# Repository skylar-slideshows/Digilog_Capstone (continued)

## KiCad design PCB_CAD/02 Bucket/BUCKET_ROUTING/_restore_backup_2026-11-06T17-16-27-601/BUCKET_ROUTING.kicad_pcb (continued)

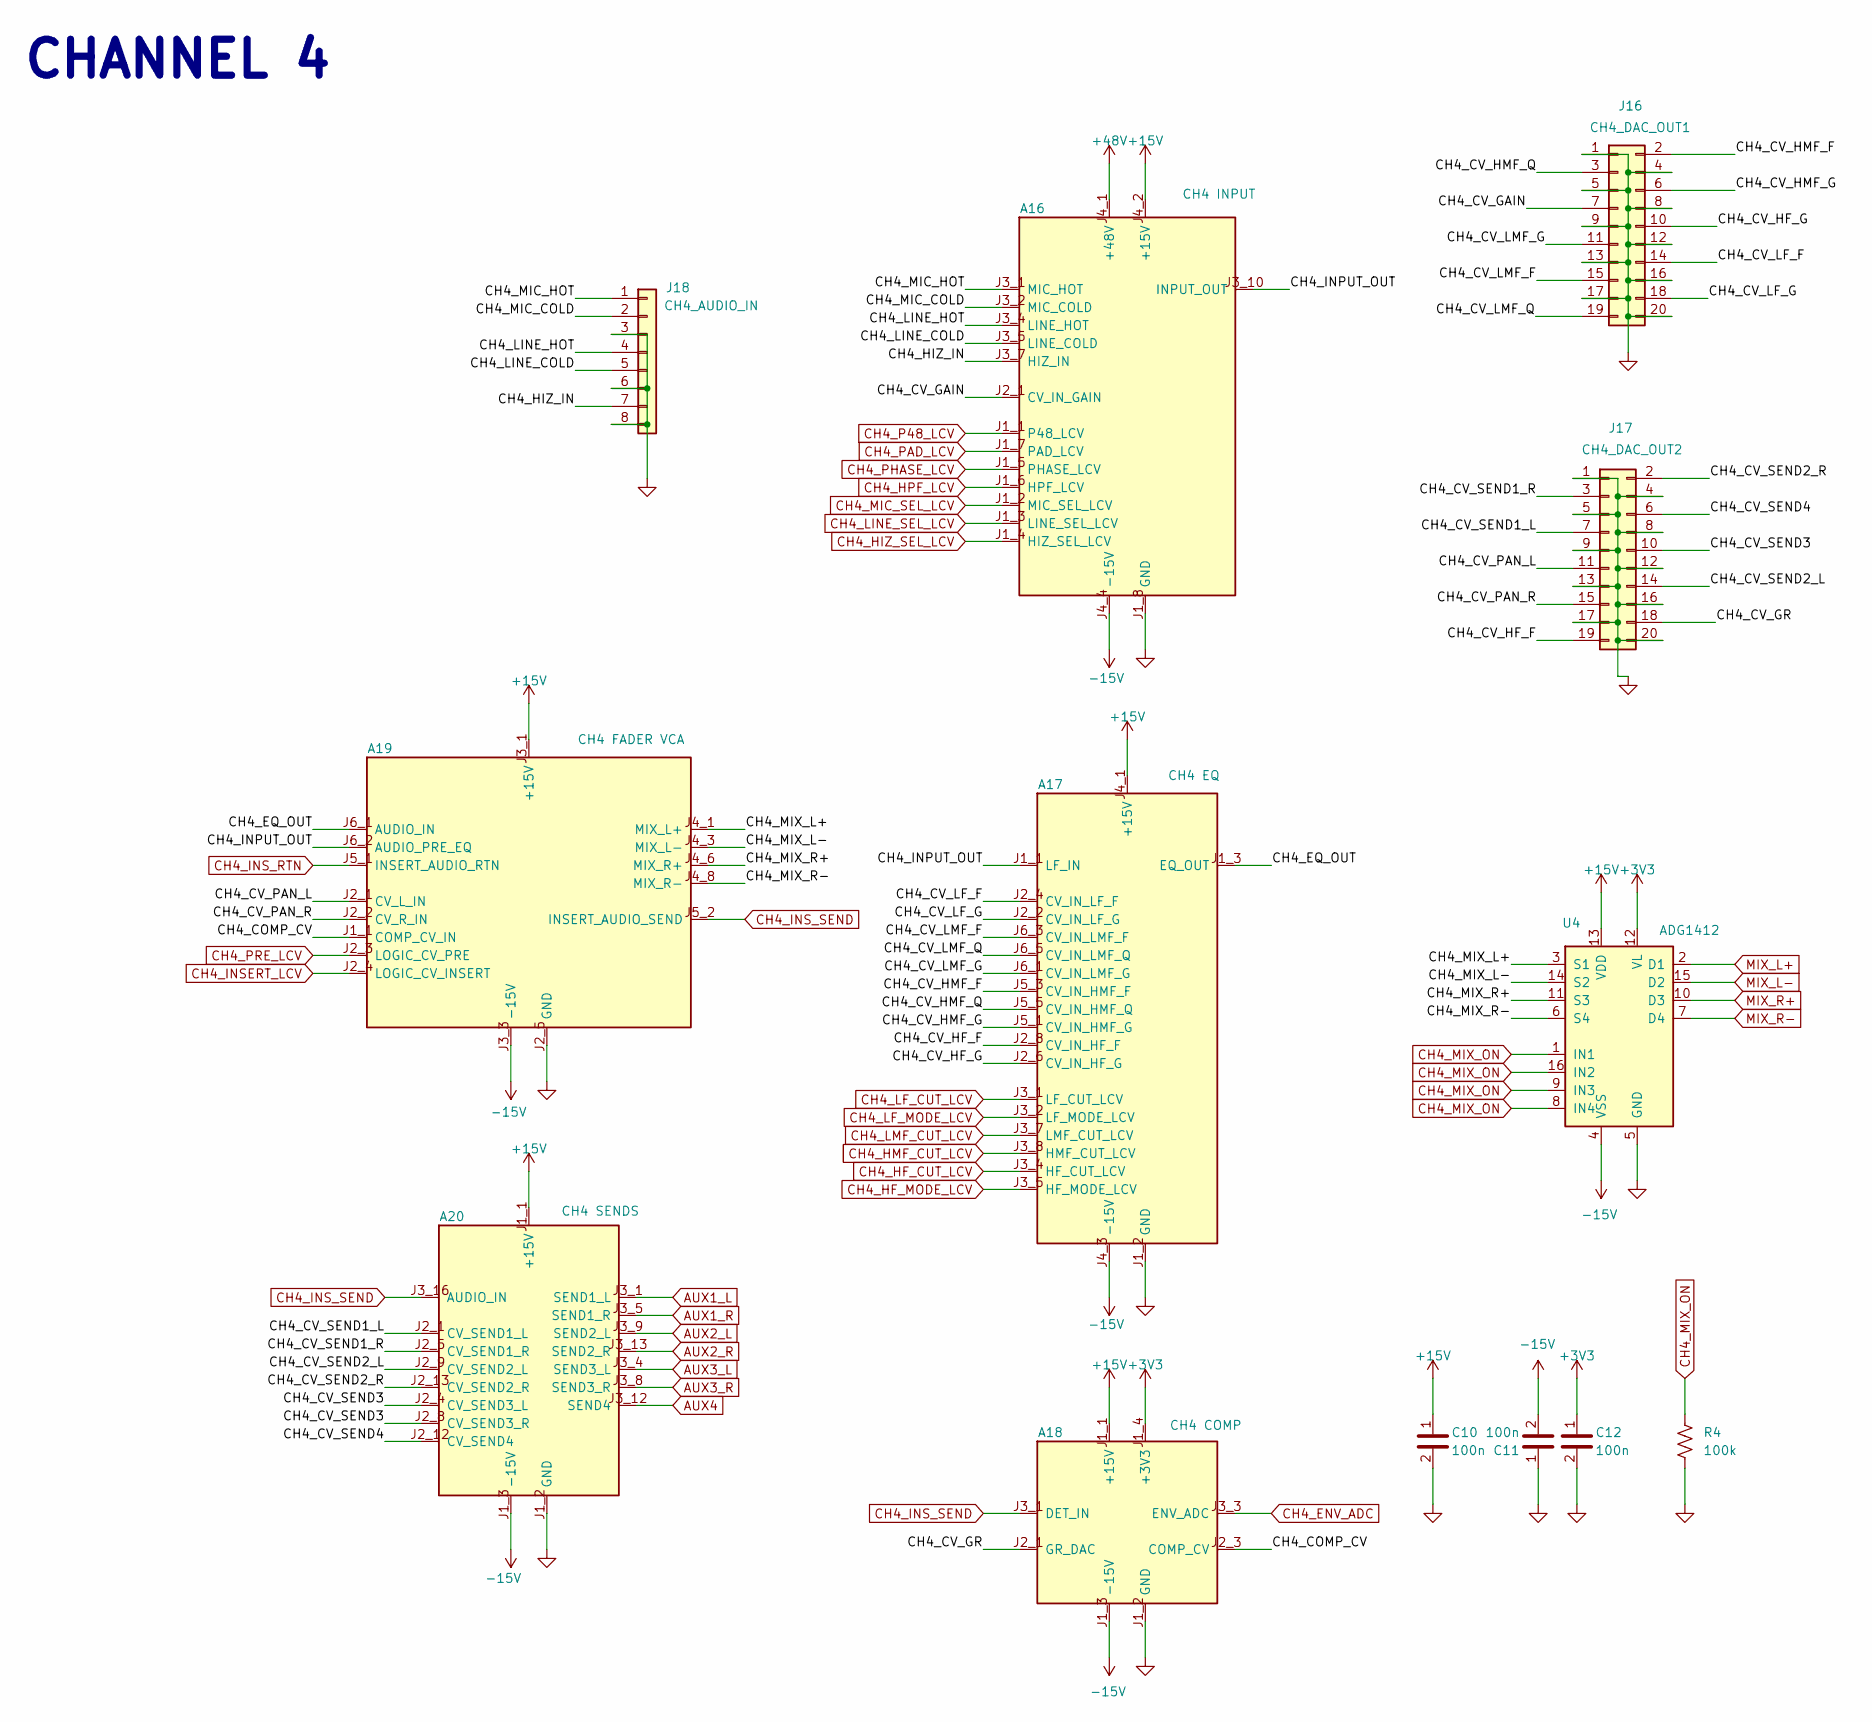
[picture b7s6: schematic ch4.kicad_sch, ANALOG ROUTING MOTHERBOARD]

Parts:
A16: CH4 INPUT; INPUT_CARD; LCSC dnp
A17: CH4 EQ; EQ_CARD; LCSC dnp
A18: CH4 COMP; COMP_CARD; LCSC dnp
A19: CH4 FADER VCA; FADER_VCA_CARD; LCSC dnp
A20: CH4 SENDS; SENDS_CARD; LCSC dnp
C10, C11, C12: 100n; C_0603_1608Metric; LCSC C1591
J16: CH4_DAC_OUT1; PinHeader_2x10_P1.27mm_Vertical; LCSC C42455943
J17: CH4_DAC_OUT2; PinHeader_2x10_P1.27mm_Vertical; LCSC C42455943
J18: CH4_AUDIO_IN; PinHeader_1x08_P2.54mm_Vertical; LCSC C54620384
R4: 100k; R_0603_1608Metric; LCSC C122538
U4: ADG1412; TSSOP-16_4.4x5mm_P0.65mm; LCSC C206604

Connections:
+3V3: A18.J1_4 (+3V3), C12.1, U4.12 (VL); also elsewhere on the board
+15V: A16.J4_2 (+15V), A17.J4_1 (+15V), A18.J1_1 (+15V), A19.J3_1 (+15V), A20.J1_1 (+15V), C10.1, U4.13 (VDD); also elsewhere on the board
+48V: A16.J4_1 (+48V); also elsewhere on the board
-15V: A16.J4_4 (-15V), A17.J4_3 (-15V), A18.J1_3 (-15V), A19.J3_3 (-15V), A20.J1_3 (-15V), C11.2, U4.4 (VSS); also elsewhere on the board
/CH4/CH4_COMP_CV: A18.J2_3 (COMP_CV), A19.J1_1 (COMP_CV_IN)
/CH4/CH4_CV_GAIN: A16.J2_1 (CV_IN_GAIN), J16.7
/CH4/CH4_CV_GR: A18.J2_1 (GR_DAC), J17.18
/CH4/CH4_CV_HF_F: A17.J2_8 (CV_IN_HF_F), J17.19
/CH4/CH4_CV_HF_G: A17.J2_6 (CV_IN_HF_G), J16.10
/CH4/CH4_CV_HMF_F: A17.J5_3 (CV_IN_HMF_F), J16.2
/CH4/CH4_CV_HMF_G: A17.J5_1 (CV_IN_HMF_G), J16.6
/CH4/CH4_CV_HMF_Q: A17.J5_5 (CV_IN_HMF_Q), J16.3
/CH4/CH4_CV_LF_F: A17.J2_4 (CV_IN_LF_F), J16.14
/CH4/CH4_CV_LF_G: A17.J2_2 (CV_IN_LF_G), J16.18
/CH4/CH4_CV_LMF_F: A17.J6_3 (CV_IN_LMF_F), J16.15
/CH4/CH4_CV_LMF_G: A17.J6_1 (CV_IN_LMF_G), J16.11
/CH4/CH4_CV_LMF_Q: A17.J6_5 (CV_IN_LMF_Q), J16.19
/CH4/CH4_CV_PAN_L: A19.J2_1 (CV_L_IN), J17.11
/CH4/CH4_CV_PAN_R: A19.J2_2 (CV_R_IN), J17.15
/CH4/CH4_CV_SEND1_L: A20.J2_1 (CV_SEND1_L), J17.7
/CH4/CH4_CV_SEND1_R: A20.J2_5 (CV_SEND1_R), J17.3
/CH4/CH4_CV_SEND2_L: A20.J2_9 (CV_SEND2_L), J17.14
/CH4/CH4_CV_SEND2_R: A20.J2_13 (CV_SEND2_R), J17.2
/CH4/CH4_CV_SEND3: A20.J2_4 (CV_SEND3_L), A20.J2_8 (CV_SEND3_R), J17.10
/CH4/CH4_CV_SEND4: A20.J2_12 (CV_SEND4), J17.6
/CH4/CH4_EQ_OUT: A17.J1_3 (EQ_OUT), A19.J6_1 (AUDIO_IN)
/CH4/CH4_HIZ_IN: A16.J3_7 (HIZ_IN), J18.7
/CH4/CH4_INPUT_OUT: A16.J3_10 (INPUT_OUT), A17.J1_1 (LF_IN), A19.J6_2 (AUDIO_PRE_EQ)
/CH4/CH4_LINE_COLD: A16.J3_5 (LINE_COLD), J18.5
/CH4/CH4_LINE_HOT: A16.J3_4 (LINE_HOT), J18.4
/CH4/CH4_MIC_COLD: A16.J3_2 (MIC_COLD), J18.2
/CH4/CH4_MIC_HOT: A16.J3_1 (MIC_HOT), J18.1
/CH4/CH4_MIX_L+: A19.J4_1 (MIX_L+), U4.3 (S1)
/CH4/CH4_MIX_L-: A19.J4_3 (MIX_L-), U4.14 (S2)
/CH4/CH4_MIX_R+: A19.J4_6 (MIX_R+), U4.11 (S3)
/CH4/CH4_MIX_R-: A19.J4_8 (MIX_R-), U4.6 (S4)
AUX1_L: A20.J3_1 (SEND1_L); also elsewhere on the board
AUX1_R: A20.J3_5 (SEND1_R); also elsewhere on the board
AUX2_L: A20.J3_9 (SEND2_L); also elsewhere on the board
AUX2_R: A20.J3_13 (SEND2_R); also elsewhere on the board
AUX3_L: A20.J3_4 (SEND3_L); also elsewhere on the board
AUX3_R: A20.J3_8 (SEND3_R); also elsewhere on the board
AUX4: A20.J3_12 (SEND4); also elsewhere on the board
CH4_ENV_ADC: A18.J3_3 (ENV_ADC); also elsewhere on the board
CH4_HF_CUT_LCV: A17.J3_4 (HF_CUT_LCV); also elsewhere on the board
CH4_HF_MODE_LCV: A17.J3_5 (HF_MODE_LCV); also elsewhere on the board
CH4_HIZ_SEL_LCV: A16.J1_4 (HIZ_SEL_LCV); also elsewhere on the board
CH4_HMF_CUT_LCV: A17.J3_8 (HMF_CUT_LCV); also elsewhere on the board
CH4_HPF_LCV: A16.J1_6 (HPF_LCV); also elsewhere on the board
CH4_INSERT_LCV: A19.J2_4 (LOGIC_CV_INSERT); also elsewhere on the board
CH4_INS_RTN: A19.J5_1 (INSERT_AUDIO_RTN); also elsewhere on the board
CH4_INS_SEND: A18.J3_1 (DET_IN), A19.J5_2 (INSERT_AUDIO_SEND), A20.J3_16 (AUDIO_IN); also elsewhere on the board
CH4_LF_CUT_LCV: A17.J3_1 (LF_CUT_LCV); also elsewhere on the board
CH4_LF_MODE_LCV: A17.J3_2 (LF_MODE_LCV); also elsewhere on the board
CH4_LINE_SEL_LCV: A16.J1_3 (LINE_SEL_LCV); also elsewhere on the board
CH4_LMF_CUT_LCV: A17.J3_7 (LMF_CUT_LCV); also elsewhere on the board
CH4_MIC_SEL_LCV: A16.J1_2 (MIC_SEL_LCV); also elsewhere on the board
CH4_MIX_ON: R4.1, U4.1 (IN1), U4.8 (IN4), U4.9 (IN3), U4.16 (IN2); also elsewhere on the board
CH4_P48_LCV: A16.J1_1 (P48_LCV); also elsewhere on the board
CH4_PAD_LCV: A16.J1_7 (PAD_LCV); also elsewhere on the board
CH4_PHASE_LCV: A16.J1_5 (PHASE_LCV); also elsewhere on the board
CH4_PRE_LCV: A19.J2_3 (LOGIC_CV_PRE); also elsewhere on the board
GND: A16.J1_8 (GND), A16.J2_2 (GND), A16.J3_3 (GND), A16.J3_6 (GND), A16.J3_8 (GND), A16.J3_9 (GND), A16.J4_3 (GND), A17.J1_2 (GND), A17.J1_4 (GND), A17.J2_1 (GND), A17.J2_3 (GND), A17.J2_5 (GND), A17.J2_7 (GND), A17.J3_3 (GND), A17.J3_6 (GND), A17.J4_2 (GND), A17.J5_2 (GND), A17.J5_4 (GND), A17.J5_6 (GND), A17.J6_2 (GND), A17.J6_4 (GND), A17.J6_6 (GND), A18.J1_2 (GND), A18.J2_2 (GND), A18.J2_4 (GND), A18.J3_2 (GND), A18.J3_4 (GND), A19.J1_2 (GND), A19.J2_5 (GND), A19.J3_2 (GND), A19.J4_2 (GND), A19.J4_4 (GND), A19.J4_5 (GND), A19.J4_7 (GND), A19.J5_3 (GND), A19.J6_3 (GND), A20.J1_2 (GND), A20.J2_2 (GND), A20.J2_3 (GND), A20.J2_6 (GND), A20.J2_7 (GND), A20.J2_10 (GND), A20.J2_11 (GND), A20.J2_14 (GND), A20.J3_2 (GND), A20.J3_3 (GND), A20.J3_6 (GND), A20.J3_7 (GND), A20.J3_10 (GND), A20.J3_11 (GND), A20.J3_14 (GND), A20.J3_15 (GND), C10.2, C11.1, C12.2, J16.1, J16.4, J16.5, J16.8, J16.9, J16.12, J16.13, J16.16, J16.17, J16.20, J17.1, J17.4, J17.5, J17.8, J17.9, J17.12, J17.13, J17.16, J17.17, J17.20, J18.3, J18.6, J18.8, R4.2, U4.5 (GND); also elsewhere on the board
MIX_L+: U4.2 (D1); also elsewhere on the board
MIX_L-: U4.15 (D2); also elsewhere on the board
MIX_R+: U4.10 (D3); also elsewhere on the board
MIX_R-: U4.7 (D4); also elsewhere on the board

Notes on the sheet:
CHANNEL 4

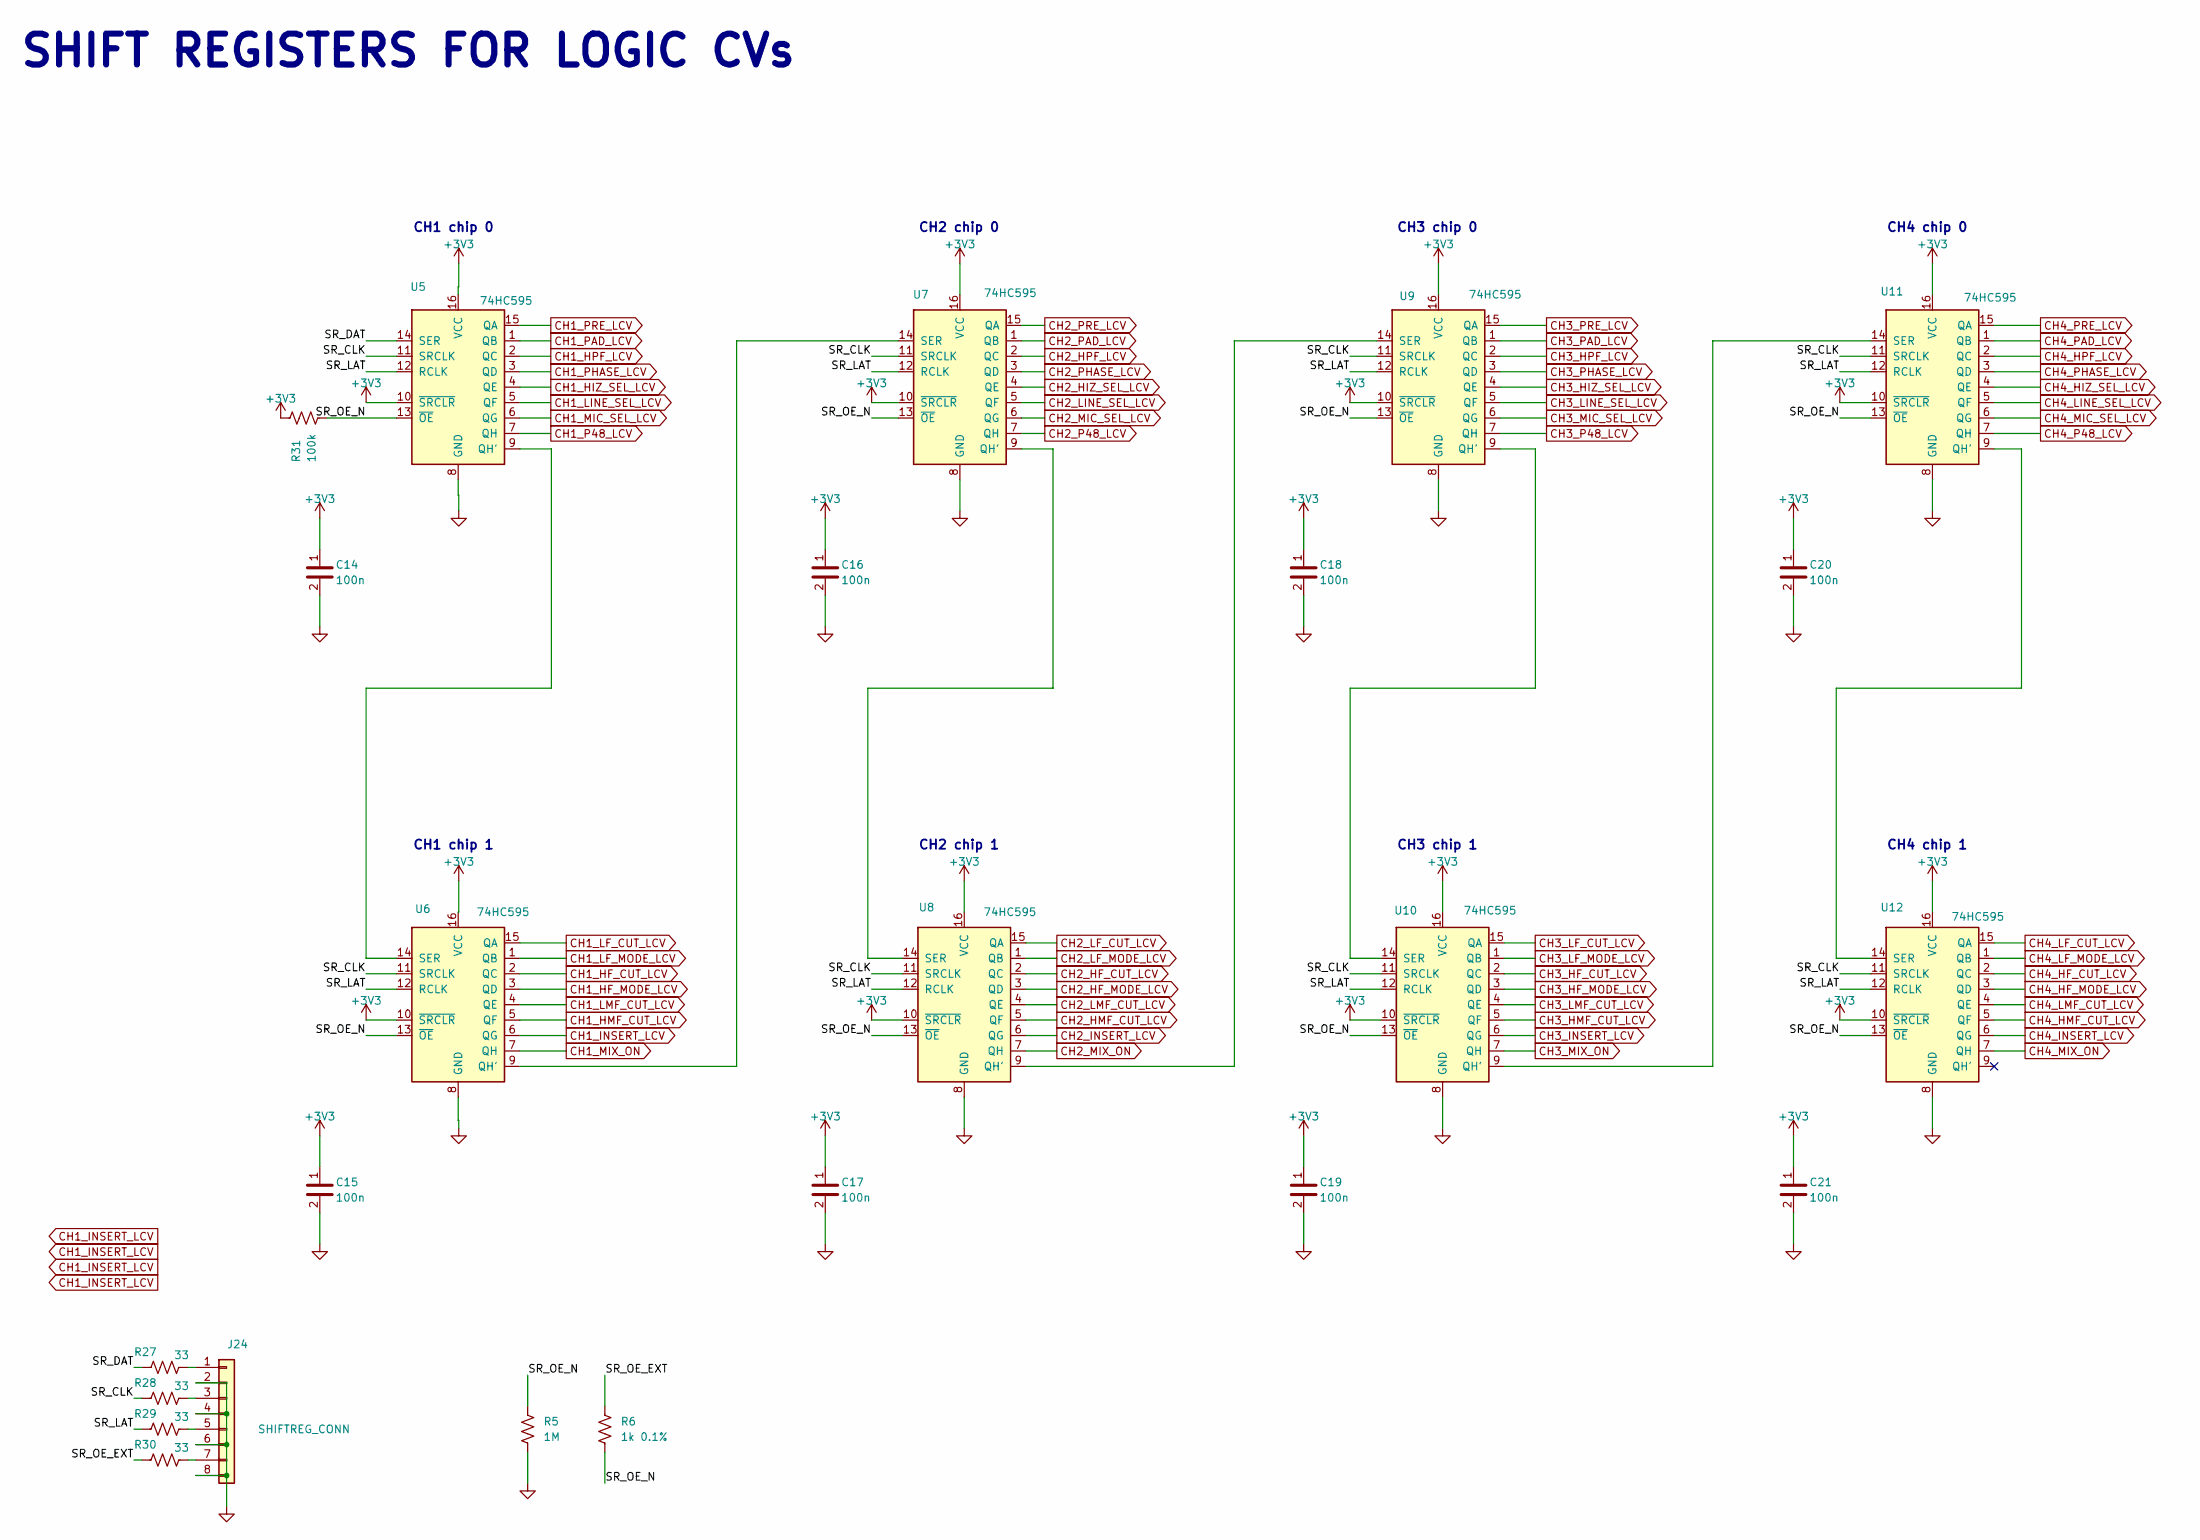
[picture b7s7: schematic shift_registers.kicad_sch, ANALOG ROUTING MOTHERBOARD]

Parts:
C14, C15, C16, C17, C18, C19, C20, C21: 100n; C_0603_1608Metric; LCSC C1591
J24: SHIFTREG_CONN; PinHeader_1x08_P2.54mm_Vertical; LCSC C54620384
R5: 1M; R_0603_1608Metric; LCSC C86472
R6: 1k 0.1%; R_0603_1608Metric; LCSC C110776
R27, R28, R29, R30: 33; R_0603_1608Metric; LCSC C23140
R31: 100k; R_0603_1608Metric; LCSC C122538
U5, U6, U7, U8, U9, U10, U11, U12: 74HC595; TSSOP-16_4.4x5mm_P0.65mm; LCSC C5948

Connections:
+3V3: C14.1, C15.1, C16.1, C17.1, C18.1, C19.1, C20.1, C21.1, R31.1, U5.10 (~SRCLR), U5.16 (VCC), U6.10 (~SRCLR), U6.16 (VCC), U7.10 (~SRCLR), U7.16 (VCC), U8.10 (~SRCLR), U8.16 (VCC), U9.10 (~SRCLR), U9.16 (VCC), U10.10 (~SRCLR), U10.16 (VCC), U11.10 (~SRCLR), U11.16 (VCC), U12.10 (~SRCLR), U12.16 (VCC); also elsewhere on the board
/LOGIC SHIFT REGISTERS/SR_CLK: J24.3, R28.1, R28.2, U5.11 (SRCLK), U6.11 (SRCLK), U7.11 (SRCLK), U8.11 (SRCLK), U9.11 (SRCLK), U10.11 (SRCLK), U11.11 (SRCLK), U12.11 (SRCLK)
/LOGIC SHIFT REGISTERS/SR_DAT: J24.1, R27.1, R27.2, U5.14 (SER)
/LOGIC SHIFT REGISTERS/SR_LAT: J24.5, R29.1, R29.2, U5.12 (RCLK), U6.12 (RCLK), U7.12 (RCLK), U8.12 (RCLK), U9.12 (RCLK), U10.12 (RCLK), U11.12 (RCLK), U12.12 (RCLK)
/LOGIC SHIFT REGISTERS/SR_OE_EXT: J24.7, R6.1, R30.1, R30.2
/LOGIC SHIFT REGISTERS/SR_OE_N: R5.1, R6.2, R31.2, U5.13 (~OE), U6.13 (~OE), U7.13 (~OE), U8.13 (~OE), U9.13 (~OE), U10.13 (~OE), U11.13 (~OE), U12.13 (~OE)
CH1_HF_CUT_LCV: U6.2 (QC); also elsewhere on the board
CH1_HF_MODE_LCV: U6.3 (QD); also elsewhere on the board
CH1_HIZ_SEL_LCV: U5.4 (QE); also elsewhere on the board
CH1_HMF_CUT_LCV: U6.5 (QF); also elsewhere on the board
CH1_HPF_LCV: U5.2 (QC); also elsewhere on the board
CH1_INSERT_LCV: U6.6 (QG); also elsewhere on the board
CH1_LF_CUT_LCV: U6.15 (QA); also elsewhere on the board
CH1_LF_MODE_LCV: U6.1 (QB); also elsewhere on the board
CH1_LINE_SEL_LCV: U5.5 (QF); also elsewhere on the board
CH1_LMF_CUT_LCV: U6.4 (QE); also elsewhere on the board
CH1_MIC_SEL_LCV: U5.6 (QG); also elsewhere on the board
CH1_MIX_ON: U6.7 (QH); also elsewhere on the board
CH1_P48_LCV: U5.7 (QH); also elsewhere on the board
CH1_PAD_LCV: U5.1 (QB); also elsewhere on the board
CH1_PHASE_LCV: U5.3 (QD); also elsewhere on the board
CH1_PRE_LCV: U5.15 (QA); also elsewhere on the board
CH2_HF_CUT_LCV: U8.2 (QC); also elsewhere on the board
CH2_HF_MODE_LCV: U8.3 (QD); also elsewhere on the board
CH2_HIZ_SEL_LCV: U7.4 (QE); also elsewhere on the board
CH2_HMF_CUT_LCV: U8.5 (QF); also elsewhere on the board
CH2_HPF_LCV: U7.2 (QC); also elsewhere on the board
CH2_INSERT_LCV: U8.6 (QG); also elsewhere on the board
CH2_LF_CUT_LCV: U8.15 (QA); also elsewhere on the board
CH2_LF_MODE_LCV: U8.1 (QB); also elsewhere on the board
CH2_LINE_SEL_LCV: U7.5 (QF); also elsewhere on the board
CH2_LMF_CUT_LCV: U8.4 (QE); also elsewhere on the board
CH2_MIC_SEL_LCV: U7.6 (QG); also elsewhere on the board
CH2_MIX_ON: U8.7 (QH); also elsewhere on the board
CH2_P48_LCV: U7.7 (QH); also elsewhere on the board
CH2_PAD_LCV: U7.1 (QB); also elsewhere on the board
CH2_PHASE_LCV: U7.3 (QD); also elsewhere on the board
CH2_PRE_LCV: U7.15 (QA); also elsewhere on the board
CH3_HF_CUT_LCV: U10.2 (QC); also elsewhere on the board
CH3_HF_MODE_LCV: U10.3 (QD); also elsewhere on the board
CH3_HIZ_SEL_LCV: U9.4 (QE); also elsewhere on the board
CH3_HMF_CUT_LCV: U10.5 (QF); also elsewhere on the board
CH3_HPF_LCV: U9.2 (QC); also elsewhere on the board
CH3_INSERT_LCV: U10.6 (QG); also elsewhere on the board
CH3_LF_CUT_LCV: U10.15 (QA); also elsewhere on the board
CH3_LF_MODE_LCV: U10.1 (QB); also elsewhere on the board
CH3_LINE_SEL_LCV: U9.5 (QF); also elsewhere on the board
CH3_LMF_CUT_LCV: U10.4 (QE); also elsewhere on the board
CH3_MIC_SEL_LCV: U9.6 (QG); also elsewhere on the board
CH3_MIX_ON: U10.7 (QH); also elsewhere on the board
CH3_P48_LCV: U9.7 (QH); also elsewhere on the board
CH3_PAD_LCV: U9.1 (QB); also elsewhere on the board
CH3_PHASE_LCV: U9.3 (QD); also elsewhere on the board
CH3_PRE_LCV: U9.15 (QA); also elsewhere on the board
CH4_HF_CUT_LCV: U12.2 (QC); also elsewhere on the board
CH4_HF_MODE_LCV: U12.3 (QD); also elsewhere on the board
CH4_HIZ_SEL_LCV: U11.4 (QE); also elsewhere on the board
CH4_HMF_CUT_LCV: U12.5 (QF); also elsewhere on the board
CH4_HPF_LCV: U11.2 (QC); also elsewhere on the board
CH4_INSERT_LCV: U12.6 (QG); also elsewhere on the board
CH4_LF_CUT_LCV: U12.15 (QA); also elsewhere on the board
CH4_LF_MODE_LCV: U12.1 (QB); also elsewhere on the board
CH4_LINE_SEL_LCV: U11.5 (QF); also elsewhere on the board
CH4_LMF_CUT_LCV: U12.4 (QE); also elsewhere on the board
CH4_MIC_SEL_LCV: U11.6 (QG); also elsewhere on the board
CH4_MIX_ON: U12.7 (QH); also elsewhere on the board
CH4_P48_LCV: U11.7 (QH); also elsewhere on the board
CH4_PAD_LCV: U11.1 (QB); also elsewhere on the board
CH4_PHASE_LCV: U11.3 (QD); also elsewhere on the board
CH4_PRE_LCV: U11.15 (QA); also elsewhere on the board
GND: C14.2, C15.2, C16.2, C17.2, C18.2, C19.2, C20.2, C21.2, J24.2, J24.4, J24.6, J24.8, R5.2, U5.8 (GND), U6.8 (GND), U7.8 (GND), U8.8 (GND), U9.8 (GND), U10.8 (GND), U11.8 (GND), U12.8 (GND); also elsewhere on the board
unnamed: U5.9 (QH'), U6.14 (SER)
unnamed: U6.9 (QH'), U7.14 (SER)
unnamed: U7.9 (QH'), U8.14 (SER)
unnamed: U8.9 (QH'), U9.14 (SER)
unnamed: U10.9 (QH'), U11.14 (SER)
unnamed: U9.9 (QH'), U10.14 (SER)
unnamed: U11.9 (QH'), U12.14 (SER)

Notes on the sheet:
CH1 chip 0
CH3 chip 1
CH1 chip 1
CH3 chip 0
CH4 chip 0
CH4 chip 1
SHIFT REGISTERS FOR LOGIC CVs
CH2 chip 1
CH2 chip 0

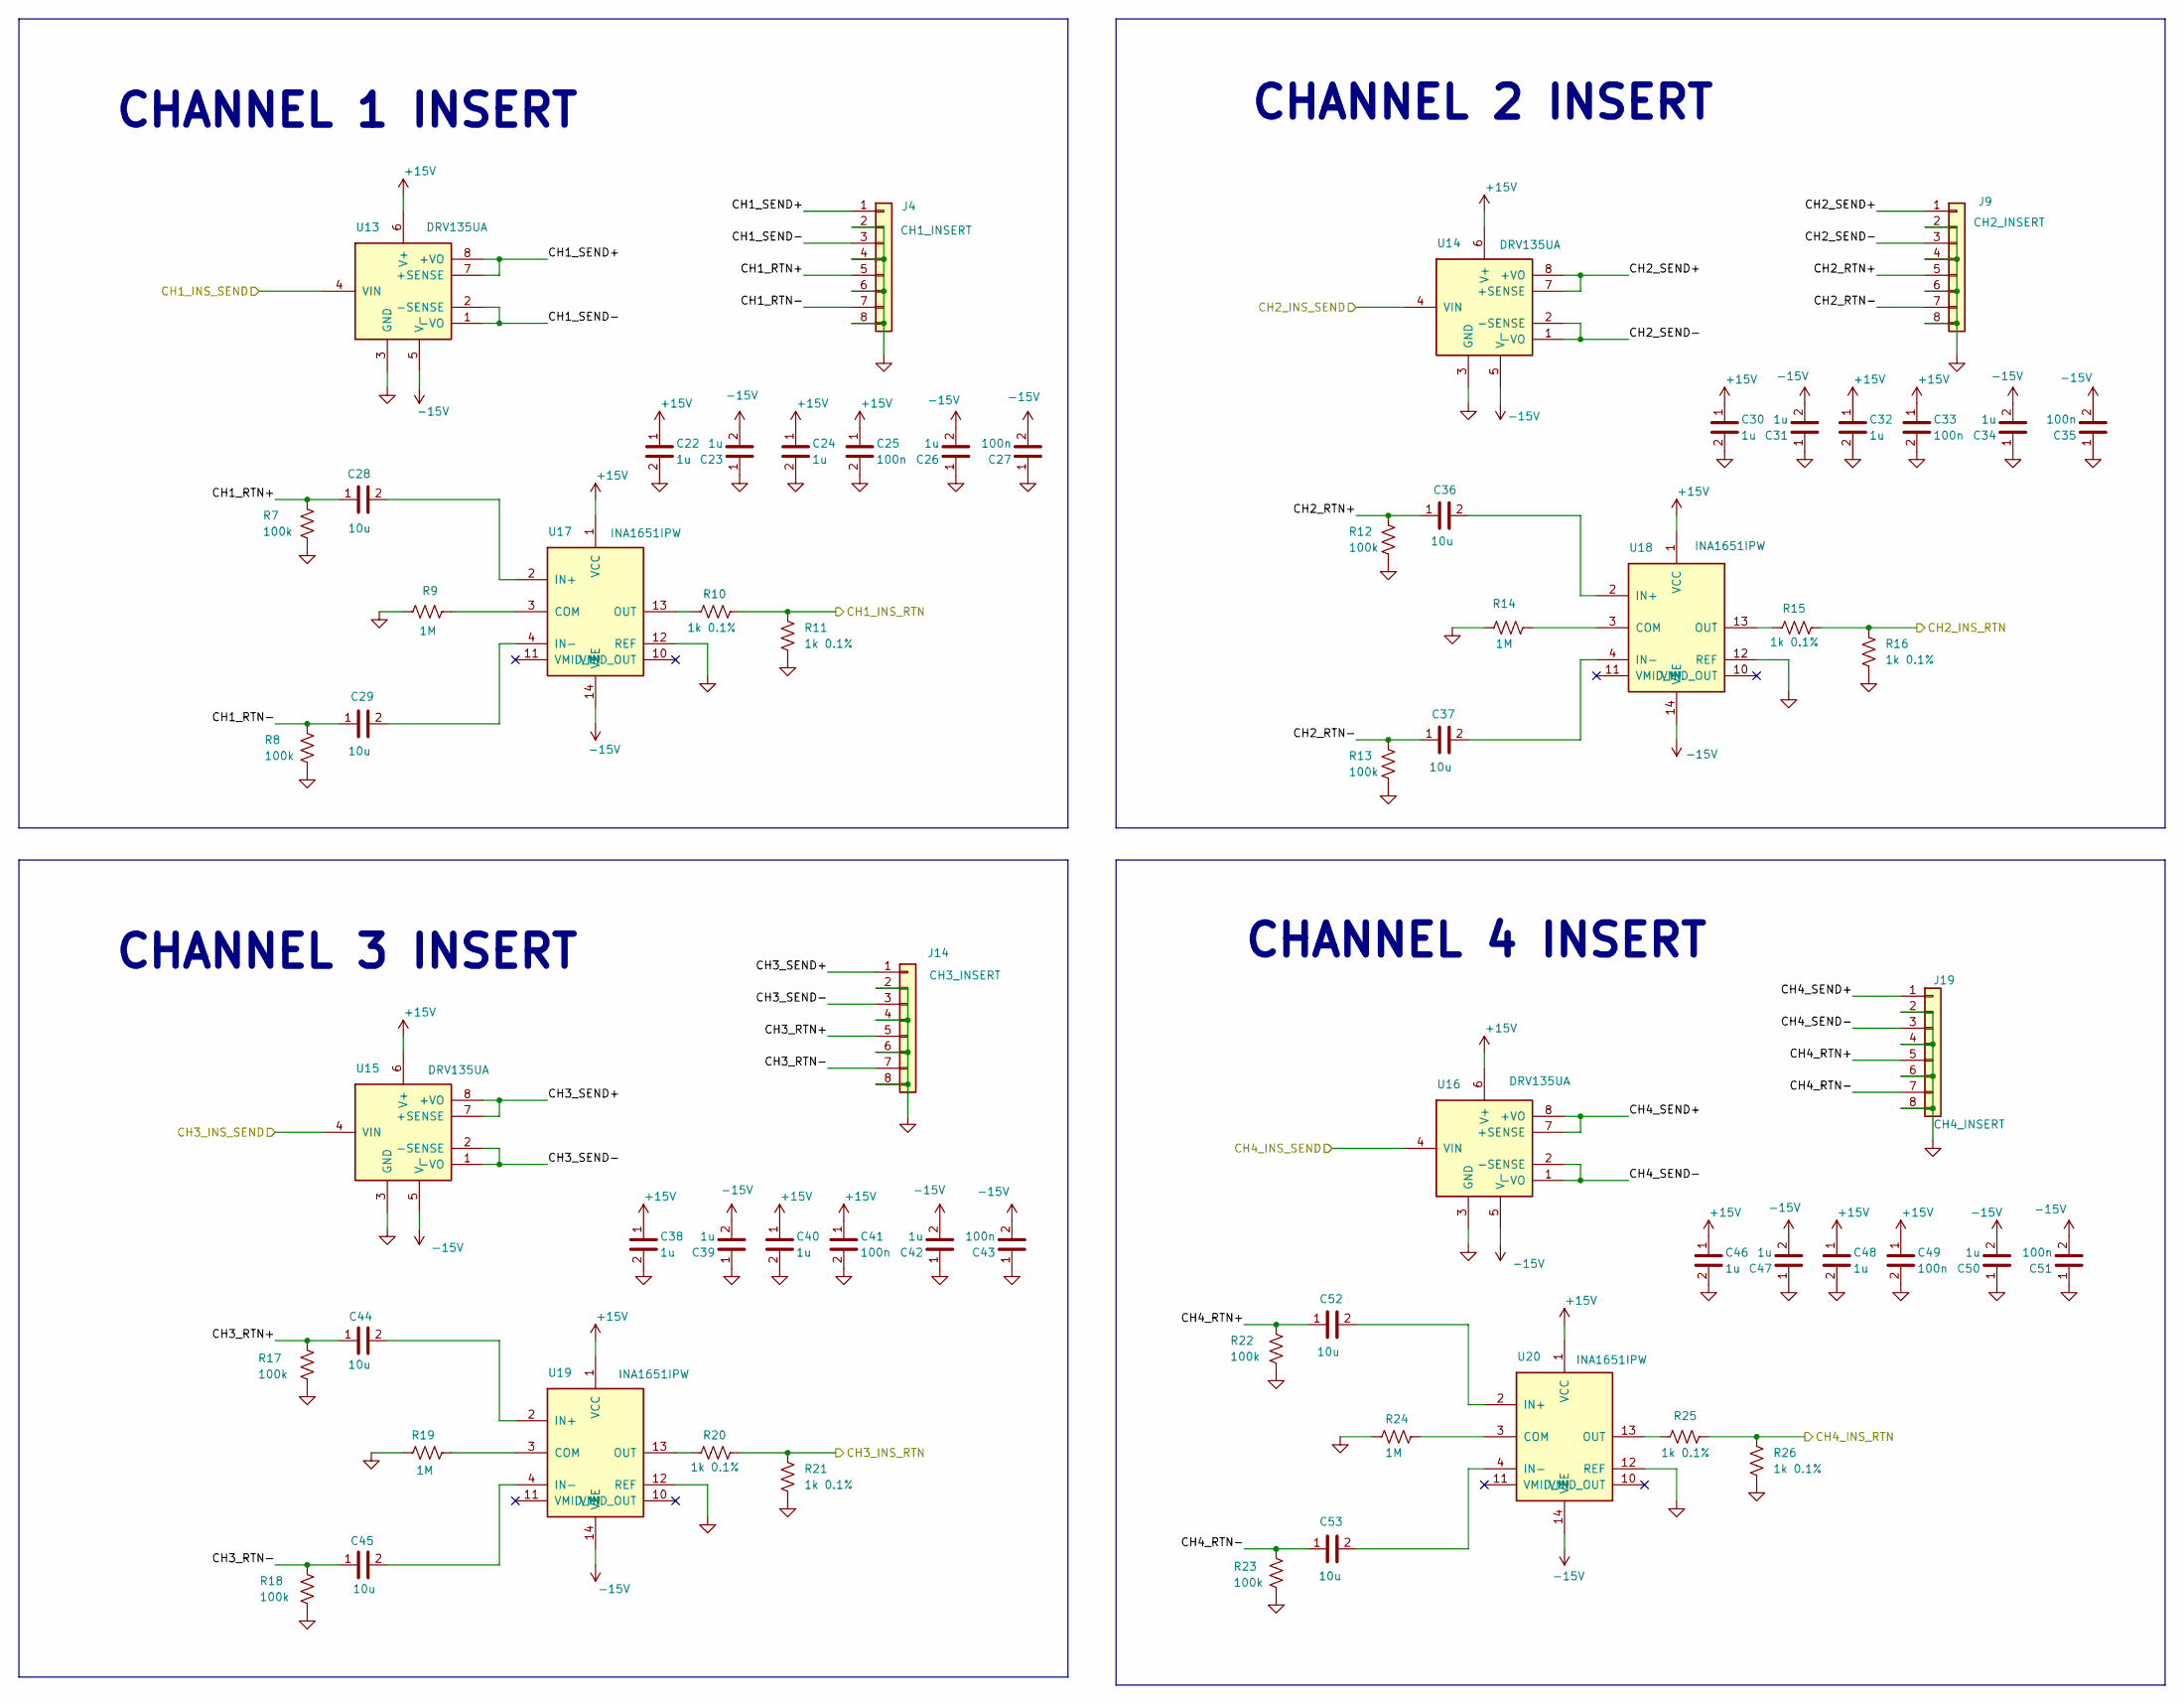
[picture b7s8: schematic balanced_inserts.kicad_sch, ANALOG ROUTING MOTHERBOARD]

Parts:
C22, C23, C24, C26, C30, C31, C32, C34, C38, C39, C40, C42, C46, C47, C48, C50: 1u; C_0603_1608Metric
C25, C27, C33, C35, C41, C43, C49, C51: 100n; C_0603_1608Metric
C28, C29, C36, C37, C44, C45, C52, C53: 10u; C_1206_3216Metric
J4: CH1_INSERT; PinHeader_1x08_P2.54mm_Vertical
J9: CH2_INSERT; PinHeader_1x08_P2.54mm_Vertical
J14: CH3_INSERT; PinHeader_1x08_P2.54mm_Vertical
J19: CH4_INSERT; PinHeader_1x08_P2.54mm_Vertical
R7, R8, R12, R13, R17, R18, R22, R23: 100k; R_0603_1608Metric
R9, R14, R19, R24: 1M; R_0603_1608Metric
R10, R11, R15, R16, R20, R21, R25, R26: 1k 0.1%; R_0603_1608Metric
U13, U14, U15, U16: DRV135UA; SOIC-8_3.9x4.9mm_P1.27mm
U17, U18, U19, U20: INA1651IPW; TSSOP-14_4.4x5mm_P0.65mm

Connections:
+15V: C22.1, C24.1, C25.1, C30.1, C32.1, C33.1, C38.1, C40.1, C41.1, C46.1, C48.1, C49.1, U13.6 (V+), U14.6 (V+), U15.6 (V+), U16.6 (V+), U17.1 (VCC), U18.1 (VCC), U19.1 (VCC), U20.1 (VCC); also elsewhere on the board
-15V: C23.2, C26.2, C27.2, C31.2, C34.2, C35.2, C39.2, C42.2, C43.2, C47.2, C50.2, C51.2, U13.5 (V-), U14.5 (V-), U15.5 (V-), U16.5 (V-), U17.14 (VEE), U18.14 (VEE), U19.14 (VEE), U20.14 (VEE); also elsewhere on the board
/BALANCED INSERTS/CH1_RTN+: C28.1, J4.5, R7.1
/BALANCED INSERTS/CH1_RTN-: C29.1, J4.7, R8.1
/BALANCED INSERTS/CH1_SEND+: J4.1, U13.7 (+SENSE), U13.8 (+VO)
/BALANCED INSERTS/CH1_SEND-: J4.3, U13.1 (-VO), U13.2 (-SENSE)
/BALANCED INSERTS/CH2_RTN+: C36.1, J9.5, R12.1
/BALANCED INSERTS/CH2_RTN-: C37.1, J9.7, R13.1
/BALANCED INSERTS/CH2_SEND+: J9.1, U14.7 (+SENSE), U14.8 (+VO)
/BALANCED INSERTS/CH2_SEND-: J9.3, U14.1 (-VO), U14.2 (-SENSE)
/BALANCED INSERTS/CH3_RTN+: C44.1, J14.5, R17.1
/BALANCED INSERTS/CH3_RTN-: C45.1, J14.7, R18.1
/BALANCED INSERTS/CH3_SEND+: J14.1, U15.7 (+SENSE), U15.8 (+VO)
/BALANCED INSERTS/CH3_SEND-: J14.3, U15.1 (-VO), U15.2 (-SENSE)
/BALANCED INSERTS/CH4_RTN+: C52.1, J19.5, R22.1
/BALANCED INSERTS/CH4_RTN-: C53.1, J19.7, R23.1
/BALANCED INSERTS/CH4_SEND+: J19.1, U16.7 (+SENSE), U16.8 (+VO)
/BALANCED INSERTS/CH4_SEND-: J19.3, U16.1 (-VO), U16.2 (-SENSE)
CH1_INS_RTN: R10.2, R11.1; also elsewhere on the board
CH1_INS_SEND: U13.4 (VIN); also elsewhere on the board
CH2_INS_RTN: R15.2, R16.1; also elsewhere on the board
CH2_INS_SEND: U14.4 (VIN); also elsewhere on the board
CH3_INS_RTN: R20.2, R21.1; also elsewhere on the board
CH3_INS_SEND: U15.4 (VIN); also elsewhere on the board
CH4_INS_RTN: R25.2, R26.1; also elsewhere on the board
CH4_INS_SEND: U16.4 (VIN); also elsewhere on the board
GND: C22.2, C23.1, C24.2, C25.2, C26.1, C27.1, C30.2, C31.1, C32.2, C33.2, C34.1, C35.1, C38.2, C39.1, C40.2, C41.2, C42.1, C43.1, C46.2, C47.1, C48.2, C49.2, C50.1, C51.1, J4.2, J4.4, J4.6, J4.8, J9.2, J9.4, J9.6, J9.8, J14.2, J14.4, J14.6, J14.8, J19.2, J19.4, J19.6, J19.8, R7.2, R8.2, R9.1, R11.2, R12.2, R13.2, R14.1, R16.2, R17.2, R18.2, R19.1, R21.2, R22.2, R23.2, R24.1, R26.2, U13.3 (GND), U14.3 (GND), U15.3 (GND), U16.3 (GND), U17.12 (REF), U18.12 (REF), U19.12 (REF), U20.12 (REF); also elsewhere on the board
unnamed: R9.2, U17.3 (COM)
unnamed: C28.2, U17.2 (IN+)
unnamed: C29.2, U17.4 (IN-)
unnamed: R10.1, U17.13 (OUT)
unnamed: R14.2, U18.3 (COM)
unnamed: C36.2, U18.2 (IN+)
unnamed: C37.2, U18.4 (IN-)
unnamed: R15.1, U18.13 (OUT)
unnamed: R19.2, U19.3 (COM)
unnamed: C44.2, U19.2 (IN+)
unnamed: C45.2, U19.4 (IN-)
unnamed: R20.1, U19.13 (OUT)
unnamed: R24.2, U20.3 (COM)
unnamed: C52.2, U20.2 (IN+)
unnamed: C53.2, U20.4 (IN-)
unnamed: R25.1, U20.13 (OUT)

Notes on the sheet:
CHANNEL 1 INSERT
CHANNEL 3 INSERT
CHANNEL 2 INSERT
CHANNEL 4 INSERT

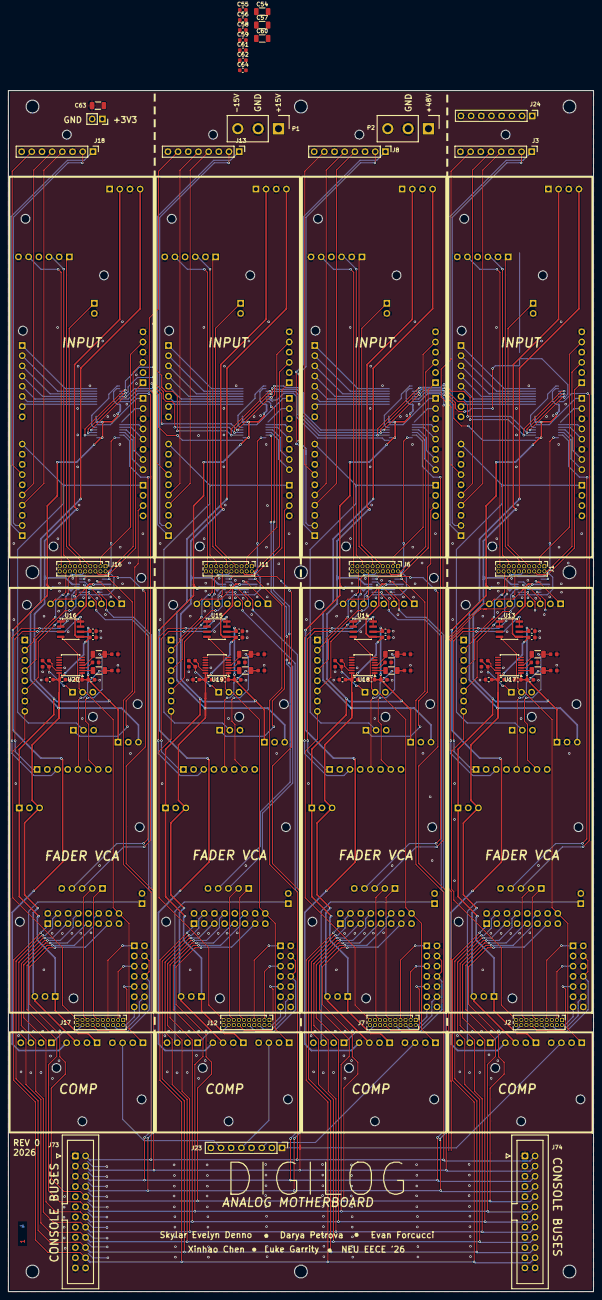
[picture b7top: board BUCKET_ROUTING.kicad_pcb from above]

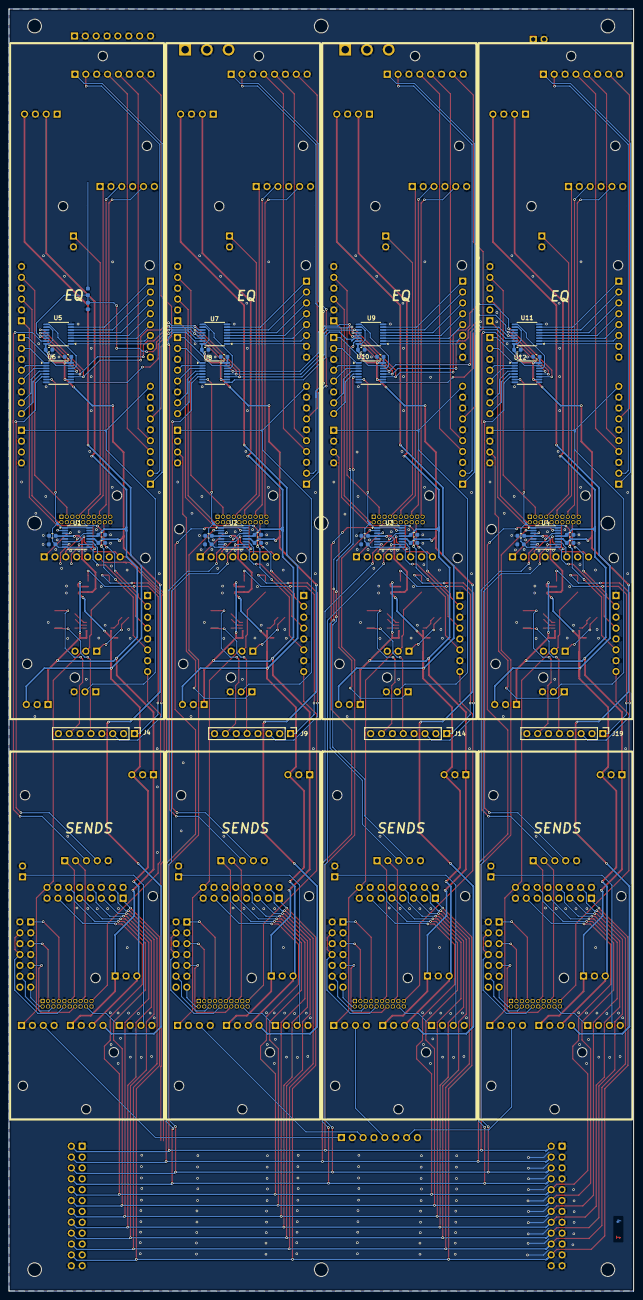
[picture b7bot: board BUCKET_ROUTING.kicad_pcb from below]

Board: 4 copper layers, 146.0 x 299.7 mm, 219 parts (115 on the bottom side), 264 nets.

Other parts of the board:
H1, H2, H3, H3#2, H4, H4#2, H4#3, H4#4, H4#5: M3 console standoff; MountingHole_3.2mm_M3

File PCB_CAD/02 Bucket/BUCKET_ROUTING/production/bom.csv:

Designator,Footprint,Quantity,Value,LCSC Part #
A1,INPUT_CARD,1,CH1 INPUT,dnp
A10,SENDS_CARD,1,CH2 SENDS,dnp
A11,INPUT_CARD,1,CH3 INPUT,dnp
A12,EQ_CARD,1,CH3 EQ,dnp
A13,COMP_CARD,1,CH3 COMP,dnp
A14,FADER_VCA_CARD,1,CH3 FADER VCA,dnp
A15,SENDS_CARD,1,CH3 SENDS,dnp
A16,INPUT_CARD,1,CH4 INPUT,dnp
A17,EQ_CARD,1,CH4 EQ,dnp
A18,COMP_CARD,1,CH4 COMP,dnp
A19,FADER_VCA_CARD,1,CH4 FADER VCA,dnp
A2,EQ_CARD,1,CH1 EQ,dnp
A20,SENDS_CARD,1,CH4 SENDS,dnp
A3,COMP_CARD,1,CH1 COMP,dnp
A4,FADER_VCA_CARD,1,CH1 FADER VCA,dnp
A5,SENDS_CARD,1,CH1 SENDS,dnp
A6,INPUT_CARD,1,CH2 INPUT,dnp
A7,EQ_CARD,1,CH2 EQ,dnp
A8,COMP_CARD,1,CH2 COMP,dnp
A9,FADER_VCA_CARD,1,CH2 FADER VCA,dnp
"C1, C10, C11, C12, C14, C15, C16, C17, C18, C19, C2, C20, C21, C25, C27, C3, C33, C35, C4, C41, C43, C49, C5, C51, C6, C7, C8, C9",0603,28,100n,C1591
"C22, C23, C24, C26, C30, C31, C32, C34, C38, C39, C40, C42, C46, C47, C48, C50",0603,16,1u,C15849
"C28, C29, C36, C37, C44, C45, C52, C53",CP_Elec_6.3x5.4_Nichicon,8,33u,C2164905
C63,1206,1,10u,C1849
"C64, C65",CP_Elec_6.3x5.4,2,47u,C3344
"H11, H12, H13, H14, H15, H16, H17, H18, H19, H20, H21, H22, H23, H24, H25, H26, H27, H28, H29, H30, H31, H32, H33, H34, H35, H36, H37, H38, H39, H41, H42, H43, H44, H45, H46, H47, H48, H49, H50, H51, H52, H53, H54, H55, H56, H57, H58, H59, H60, H61, H62, H63, H64, H65, H66, H7, H8, H9",MountingHole_2.2mm_M2,58,MountingHole,dnp
J1,PinHeader_2x10_P1.27mm_Vertical,1,CH1_DAC_OUT1,C42455943
J11,PinHeader_2x10_P1.27mm_Vertical,1,CH3_DAC_OUT1,C42455943
J12,PinHeader_2x10_P1.27mm_Vertical,1,CH3_DAC_OUT2,C42455943
J13,PinHeader_1x08_P2.54mm_Vertical,1,CH3_AUDIO_IN,C54620384
J14,PinHeader_1x08_P2.54mm_Vertical,1,CH3_INSERT,C54620384
J16,PinHeader_2x10_P1.27mm_Vertical,1,CH4_DAC_OUT1,C42455943
J17,PinHeader_2x10_P1.27mm_Vertical,1,CH4_DAC_OUT2,C42455943
J18,PinHeader_1x08_P2.54mm_Vertical,1,CH4_AUDIO_IN,C54620384
J19,PinHeader_1x08_P2.54mm_Vertical,1,CH4_INSERT,C54620384
J2,PinHeader_2x10_P1.27mm_Vertical,1,CH1_DAC_OUT2,C42455943
J23,PinHeader_1x08_P2.54mm_Vertical,1,ENV_TO_CONTROLLER,C54620384
J24,PinHeader_1x08_P2.54mm_Vertical,1,SHIFTREG_CONN,C54620384
J3,PinHeader_1x08_P2.54mm_Vertical,1,CH1_AUDIO_IN,C54620384
J4,PinHeader_1x08_P2.54mm_Vertical,1,CH1_INSERT,C54620384
J6,PinHeader_2x10_P1.27mm_Vertical,1,CH2_DAC_OUT1,C42455943
J7,PinHeader_2x10_P1.27mm_Vertical,1,CH2_DAC_OUT2,C42455943
J73,IDC-Header_2x12_P2.54mm_Vertical,1,BUS_A_MIX_AUX,C53207829
J74,IDC-Header_2x12_P2.54mm_Vertical,1,BUS_B_MIX_AUX,C53207829
J8,PinHeader_1x08_P2.54mm_Vertical,1,CH2_AUDIO_IN,C54620384
J9,PinHeader_1x08_P2.54mm_Vertical,1,CH2_INSERT,C54620384
P1,Samtec_HPM-03-05-x-S_Straight_1x03_Pitch5.08mm,1,PWR_IN_+-15V,dnp
P2,Samtec_HPM-03-05-x-S_Straight_1x03_Pitch5.08mm,1,PWR_IN_+48V,dnp
P3,PinSocket_1x02_P2.54mm_Vertical,1,PWR_IN_+3V3,C5360898
"R1, R12, R13, R17, R18, R2, R22, R23, R3, R31, R4, R7, R8",0603,13,100k,C122538
"R10, R11, R15, R16, R20, R21, R25, R26, R6",0603,9,1k 0.1%,C110776
"R14, R19, R24, R5, R9",0603,5,1M,C86472
"R27, R28, R29, R30",0603,4,33,C23140
"U1, U2, U3, U4",TSSOP-16_4.4x5mm_P0.65mm,4,ADG1412,C206604
"U10, U11, U12, U5, U6, U7, U8, U9",TSSOP-16_4.4x5mm_P0.65mm,8,74HC595,C5948
"U13, U14, U15, U16",SOIC-8_3.9x4.9mm_P1.27mm,4,DRV135UA,C544663
"U17, U18, U19, U20",TSSOP-14_4.4x5mm_P0.65mm,4,INA1651IPW,dnp
